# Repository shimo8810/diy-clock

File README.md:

# Rust Board

## Purpose

This project is intended for my personal study and information sharing. The main objectives are as follows:

### Practicing Electronics Circuit

Being a complete novice in circuit design, I created a simple hobby board for the purpose of studying circuit and PCB design.

### Gathering Information on Embedded Rust

The knowledge of developing embedded systems using Rust are scattered, so I wanted to compile information for myself. While there is a wealth of development information available for well-known boards, there is limited knowledge on directly controlling microcontrollers.

## Electronics Circuit

## FirmWare

### connection

In this project, I use FT232RL to write firmware to this board. The connection between FT232RL and the clock's ISP pins should be made according to the table below. Please note that the current version has a design flaw in the ISP pin layout, which deviates from the standard ISP pin configuration. It has become confusing and inconvenient due to this misleading and unfortunate design. Therefore, caution should be exercised.

| FT232RL |    PIN    |
| :-----: | :-------: |
|   CTS   | ISP_MISO  |
|   DCD   | ISP_MOSI  |
|   DSR   |  ISP_SCK  |
|   RI    | ISP_RESET |
|   VCC   |    5V     |
|   GND   |    GND    |

### writing

I use avrdude for writing the firmware. Writing can be performed with the following command. When writing for the first time, it is necessary to configure the fuse settings for attiny2313. Since we are running attiny2313 with an external oscillator (16MHz) and no prescaler, please write with the following settings.

```sh
avrdude -c diecimila \
        -p t2313 \
        -U flash:w:./target/avr-attiny2313/release/blink-attiny2313.elf:e \
        -U lfuse:w:0xff:m
```

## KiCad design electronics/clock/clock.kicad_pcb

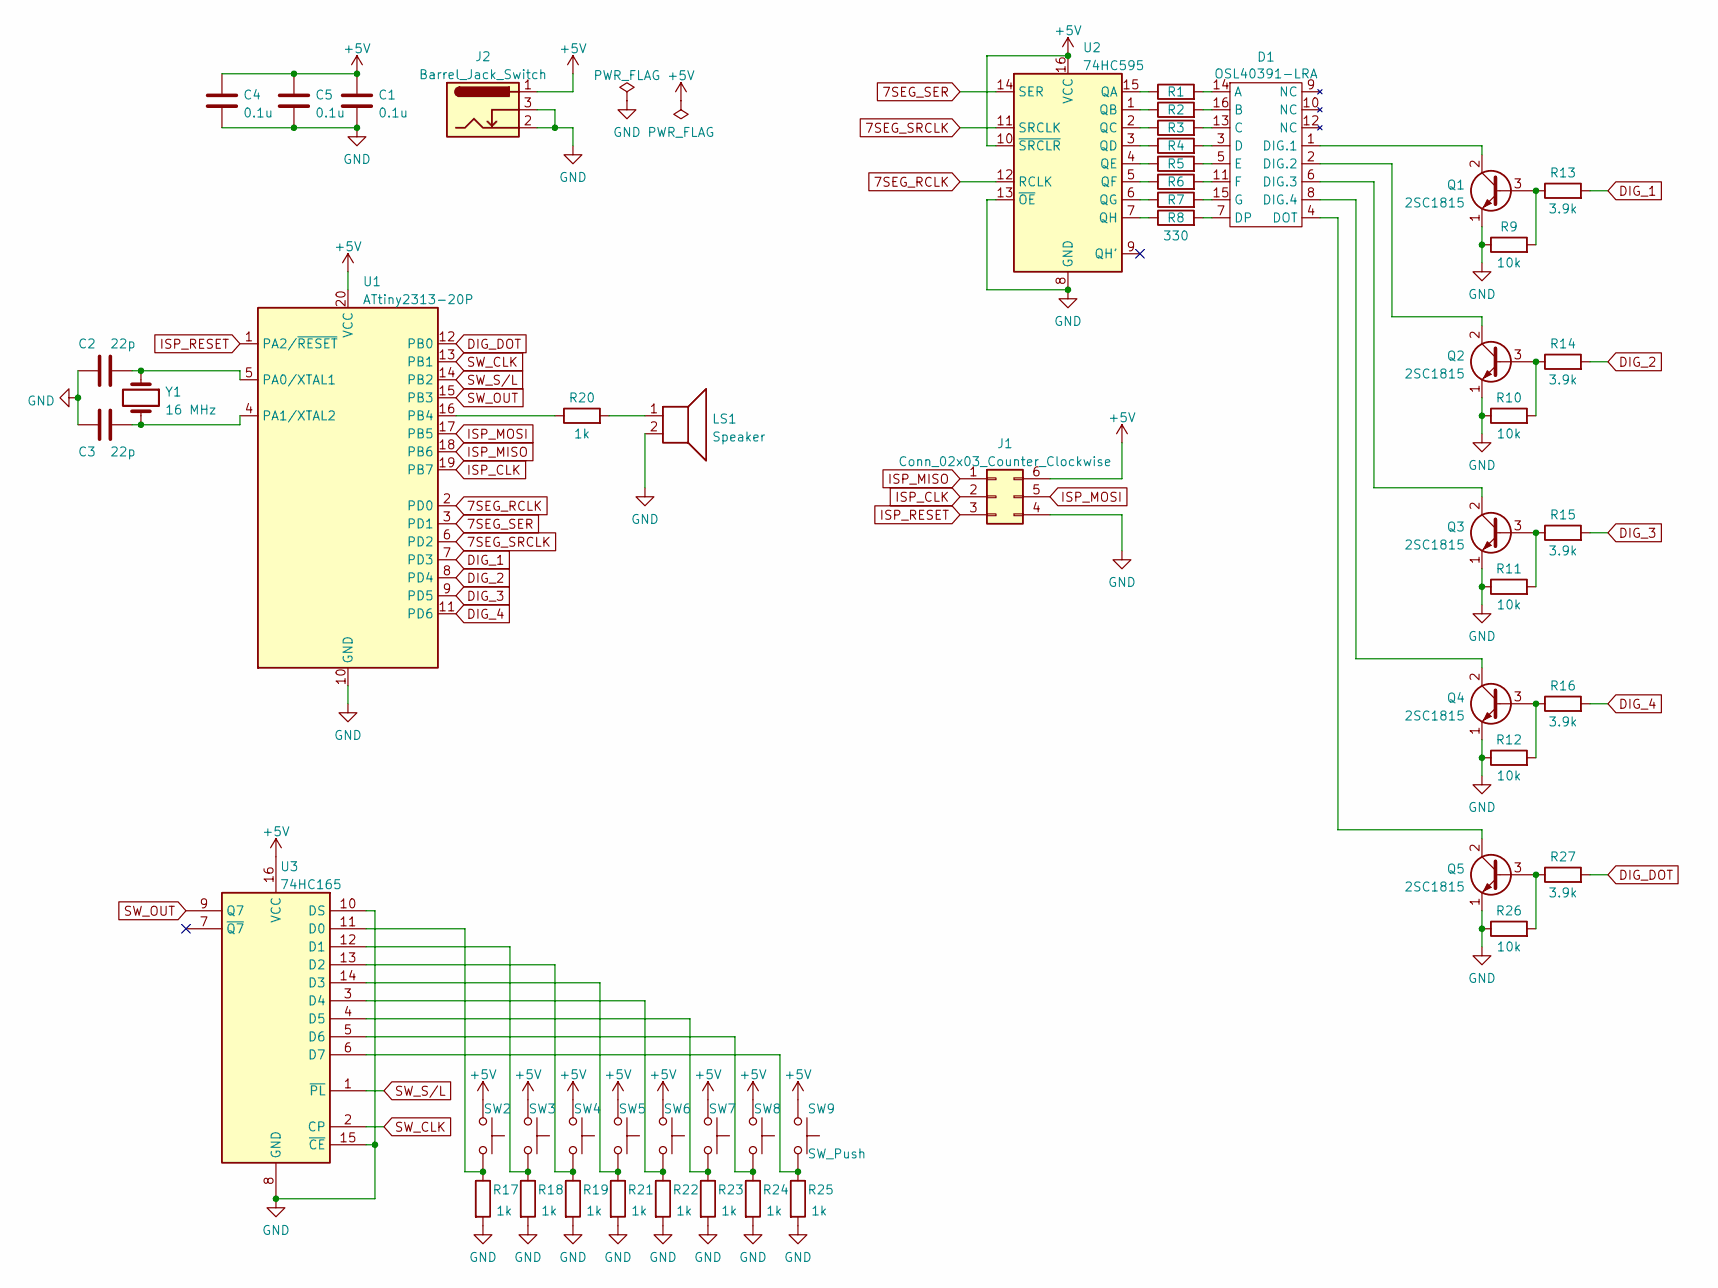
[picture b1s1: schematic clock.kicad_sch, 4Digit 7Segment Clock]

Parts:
C1, C4, C5: 0.1u; C_Disc_D3.0mm_W1.6mm_P2.50mm
C2, C3: 22p; C_Disc_D3.0mm_W1.6mm_P2.50mm
D1: OSL40391-LRA
J1: Conn_02x03_Counter_Clockwise; PinHeader_2x03_P2.54mm_Vertical
J2: Barrel_Jack_Switch; BarrelJack_Horizontal
LS1: Speaker; Buzzer_TDK_PS1240P02BT_D12.2mm_H6.5mm
Q1, Q2, Q3, Q4, Q5: 2SC1815; TO-92_Inline
R1, R2, R3, R4, R5, R6, R7, R8: 330; R_Axial_DIN0207_L6.3mm_D2.5mm_P7.62mm_Horizontal
R9, R10, R11, R12, R26: 10k; R_Axial_DIN0207_L6.3mm_D2.5mm_P7.62mm_Horizontal
R13, R14, R15, R16, R27: 3.9k; R_Axial_DIN0207_L6.3mm_D2.5mm_P7.62mm_Horizontal
R17, R18, R19, R20, R21, R22, R23, R24, R25: 1k; R_Axial_DIN0207_L6.3mm_D2.5mm_P7.62mm_Horizontal
SW2, SW3, SW4, SW5, SW6, SW7, SW8, SW9: SW_Push; SW_PUSH_6mm_H5mm
U1: ATtiny2313-20P; DIP-20_W7.62mm
U2: 74HC595; DIP-16_W7.62mm
U3: 74HC165; DIP-16_W7.62mm
Y1: 16 MHz; Crystal_HC18-U_Vertical

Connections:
7SEG_RCLK: U1.2 (PD0), U2.12 (RCLK)
7SEG_SER: U1.3 (PD1), U2.14 (SER)
7SEG_SRCLK: U1.6 (PD2), U2.11 (SRCLK)
+5V: C1.1, C4.1, C5.1, J1.6, J2.1, SW2.1, SW3.1, SW4.1, SW5.1, SW6.1, SW7.1, SW8.1, SW9.1, U1.20 (VCC), U2.10 (~SRCLR), U2.16 (VCC), U3.16 (VCC)
DIG_1: R13.2, U1.7 (PD3)
DIG_2: R14.2, U1.8 (PD4)
DIG_3: R15.2, U1.9 (PD5)
DIG_4: R16.2, U1.11 (PD6)
DIG_DOT: R27.2, U1.12 (PB0)
GND: C1.2, C2.1, C3.1, C4.2, C5.2, J1.4, J2.2, J2.3, LS1.2, Q1.1 (E), Q2.1 (E), Q3.1 (E), Q4.1 (E), Q5.1 (E), R9.1, R10.1, R11.1, R12.1, R17.2, R18.2, R19.2, R21.2, R22.2, R23.2, R24.2, R25.2, R26.1, U1.10 (GND), U2.8 (GND), U2.13 (~OE), U3.8 (GND), U3.10 (DS), U3.15 (~CE)
ISP_CLK: J1.2, U1.19 (PB7)
ISP_MISO: J1.1, U1.18 (PB6)
ISP_MOSI: J1.5, U1.17 (PB5)
ISP_RESET: J1.3, U1.1 (PA2/~RESET)
unnamed: C2.2, U1.5 (PA0/XTAL1), Y1.1
unnamed: C3.2, U1.4 (PA1/XTAL2), Y1.2
unnamed: D1.1 (DIG.1), Q1.2 (C)
unnamed: D1.2 (DIG.2), Q2.2 (C)
unnamed: D1.3 (D), R4.2
unnamed: D1.4 (DOT), Q5.2 (C)
unnamed: D1.5 (E), R5.2
unnamed: D1.6 (DIG.3), Q3.2 (C)
unnamed: D1.7 (DP), R8.2
unnamed: D1.8 (DIG.4), Q4.2 (C)
unnamed: D1.11 (F), R6.2
unnamed: D1.13 (C), R3.2
unnamed: D1.14 (A), R1.2
unnamed: D1.15 (G), R7.2
unnamed: D1.16 (B), R2.2
unnamed: LS1.1, R20.2
unnamed: Q1.3 (B), R9.2, R13.1
unnamed: Q2.3 (B), R10.2, R14.1
unnamed: Q3.3 (B), R11.2, R15.1
unnamed: Q4.3 (B), R12.2, R16.1
unnamed: Q5.3 (B), R26.2, R27.1
unnamed: R1.1, U2.15 (QA)
unnamed: R2.1, U2.1 (QB)
unnamed: R3.1, U2.2 (QC)
unnamed: R4.1, U2.3 (QD)
unnamed: R5.1, U2.4 (QE)
unnamed: R6.1, U2.5 (QF)
unnamed: R7.1, U2.6 (QG)
unnamed: R8.1, U2.7 (QH)
unnamed: R17.1, SW2.2, U3.11 (D0)
unnamed: R18.1, SW3.2, U3.12 (D1)
unnamed: R19.1, SW4.2, U3.13 (D2)
unnamed: R20.1, U1.16 (PB4)
unnamed: R21.1, SW5.2, U3.14 (D3)
unnamed: R22.1, SW6.2, U3.3 (D4)
unnamed: R23.1, SW7.2, U3.4 (D5)
unnamed: R24.1, SW8.2, U3.5 (D6)
unnamed: R25.1, SW9.2, U3.6 (D7)
SW_CLK: U1.13 (PB1), U3.2 (CP)
SW_OUT: U1.15 (PB3), U3.9 (Q7)
SW_S/L: U1.14 (PB2), U3.1 (~PL)

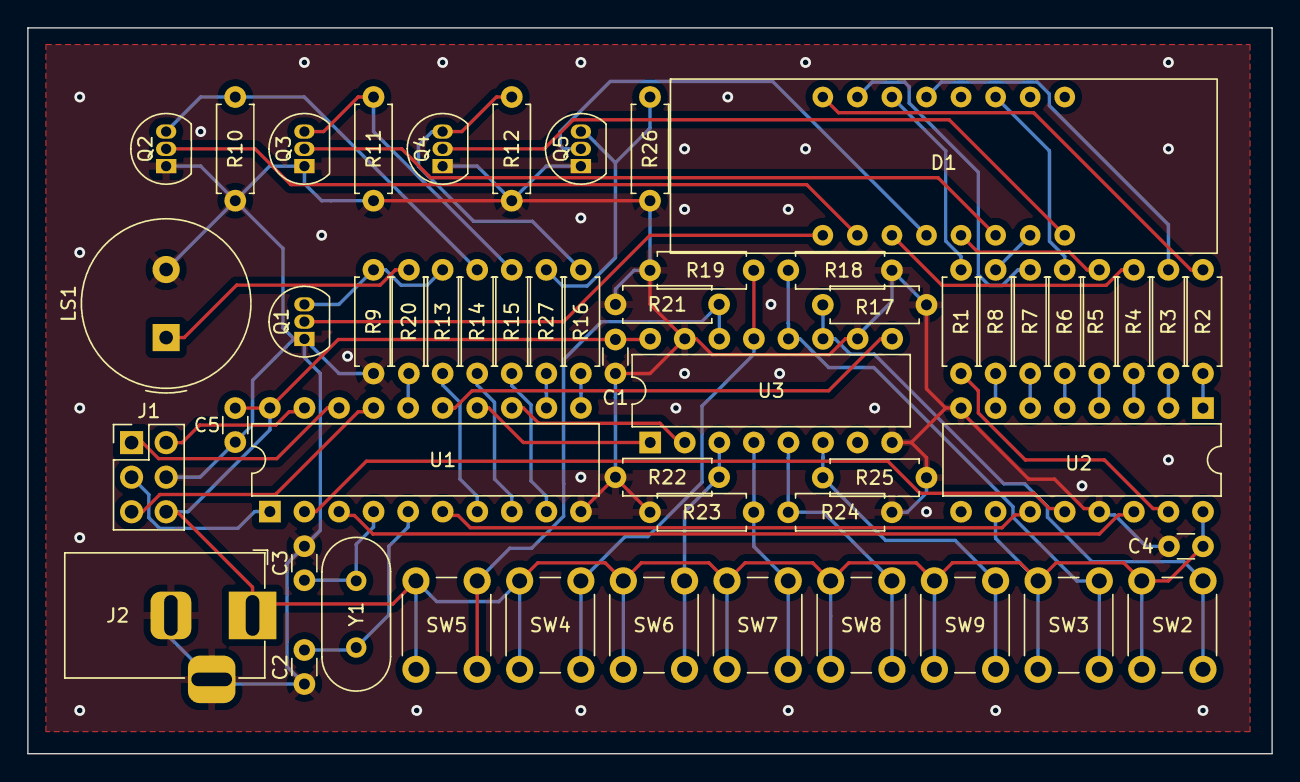
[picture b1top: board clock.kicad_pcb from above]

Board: 2 copper layers, 91.4 x 53.3 mm, 53 parts (0 on the bottom side), 55 nets.

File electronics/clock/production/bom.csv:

Designator,Footprint,Quantity,Value,LCSC Part #
"C1, C4, C5",C_Disc_D3.0mm_W1.6mm_P2.50mm,3,0.1u,
"C2, C3",C_Disc_D3.0mm_W1.6mm_P2.50mm,2,22p,
D1,OSL40391-LRA,1,OSL40391-LRA,
J1,PinHeader_2x03_P2.54mm_Vertical,1,Conn_02x03_Counter_Clockwise,
J2,BarrelJack_Horizontal,1,Barrel_Jack_Switch,
LS1,Buzzer_TDK_PS1240P02BT_D12.2mm_H6.5mm,1,Speaker,
"Q1, Q2, Q3, Q4, Q5",TO-92_Inline,5,2SC1815,
"R1, R2, R3, R4, R5, R6, R7, R8",R_Axial_DIN0207_L6.3mm_D2.5mm_P7.62mm_Horizontal,8,330,
"R10, R11, R12, R26, R9",R_Axial_DIN0207_L6.3mm_D2.5mm_P7.62mm_Horizontal,5,10k,
"R13, R14, R15, R16, R27",R_Axial_DIN0207_L6.3mm_D2.5mm_P7.62mm_Horizontal,5,3.9k,
"R17, R18, R19, R20, R21, R22, R23, R24, R25",R_Axial_DIN0207_L6.3mm_D2.5mm_P7.62mm_Horizontal,9,1k,
"SW2, SW3, SW4, SW5, SW6, SW7, SW8, SW9",SW_PUSH_6mm_H5mm,8,SW_Push,
U1,DIP-20_W7.62mm,1,ATtiny2313-20P,
U2,DIP-16_W7.62mm,1,74HC595,
U3,DIP-16_W7.62mm,1,74HC165,
Y1,Crystal_HC18-U_Vertical,1,16 MHz,

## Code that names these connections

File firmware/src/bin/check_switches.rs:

#![no_std]
#![no_main]

use attiny_hal as hal;

use firmware::ssd;

use firmware::switches::{state2number, Edge, Switches};

#[hal::entry]
fn main() -> ! {
    let dp = hal::Peripherals::take().unwrap();
    let pins: hal::Pins = hal::pins!(dp);

    let mut ssd = ssd::Ssd::new(
        pins.pd0.into_output(),
        pins.pd1.into_output(),
        pins.pd2.into_output(),
        pins.pd3.into_output(),
        pins.pd4.into_output(),
        pins.pd5.into_output(),
        pins.pd6.into_output(),
        pins.pb0.into_output(),
    );
    ssd.light_off();

    let mut switches = Switches::new(
        pins.pb1.into_output(),
        pins.pb2.into_output(),
        pins.pb3.into_floating_input(),
    );

    loop {
        let state = switches.state(Edge::No);
        let number = state2number(&state) as usize;
        ssd.display_number(number, false);
    }
}

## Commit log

2023-06-22 [add] init commit
2023-06-22 [add] add i
2023-06-22 [remove] exclude unwanted backup files
2023-06-22 [update] rename title
2023-07-03 [update] v0.0.1を作成
2023-07-03 [add] added images
2023-07-09 [add] added firmware code
2023-07-09 [update] added firmware infomation
2023-07-09 [move] move .gitignore file to a different directory.
2023-07-09 [remove] removed arduino code
2023-07-09 [add] Add firmware implemented in Rust
2023-07-09 [update] separate delay implementation into a separate file
2023-07-09 [update] separate SSD implementation into a separate file
2023-07-09 [update] separate implementation of SSD and delay
2023-07-09 [style] modify long command for improved readability by breaking it into multiple lines
2023-07-11 feat: display four-digit numbers collectively
2023-07-11 chore: add avr-device crate
    to use timer interrupts, PAC-level access is required
2023-07-11 feat: implement time counting with timer interrupts
2023-07-11 chrone: move to `./scripts` directory
2023-07-11 chore: add purpose
2023-07-11 chore: rename from images to assets
2023-07-11 chore: change images path
2023-07-12 chore: support multi-binary
2023-07-12 chore: change to multi-binaly
2023-07-12 refactor: convert into lib.rs
2023-07-14 feat: implement operation of tactile switch
2023-07-14 feat: add firmware to verify the operation of tactile switch
2023-07-14 feat: add firmware for the counter
2023-07-14 feat: add switches and panic to the library
2023-07-14 feat: implement custom panic to display panic on SSD.
2023-07-14 feat: add functionality for displaying panic
2023-07-14 refactor: remove unnecessary comments and crates
2023-07-14 chore: add configuration for newly added binary
